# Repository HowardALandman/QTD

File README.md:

# QTD
Research project on Quantum Time Dilation, including theory and plans for an experiment to test it.
For theory, see the doc/QuantumTime.pdf (or .tex) file, and the references therein.
For photos, see FB album https://www.facebook.com/howard.a.landman/media_set?set=a.10153244377383214.1073741833.690298213&type=3 .

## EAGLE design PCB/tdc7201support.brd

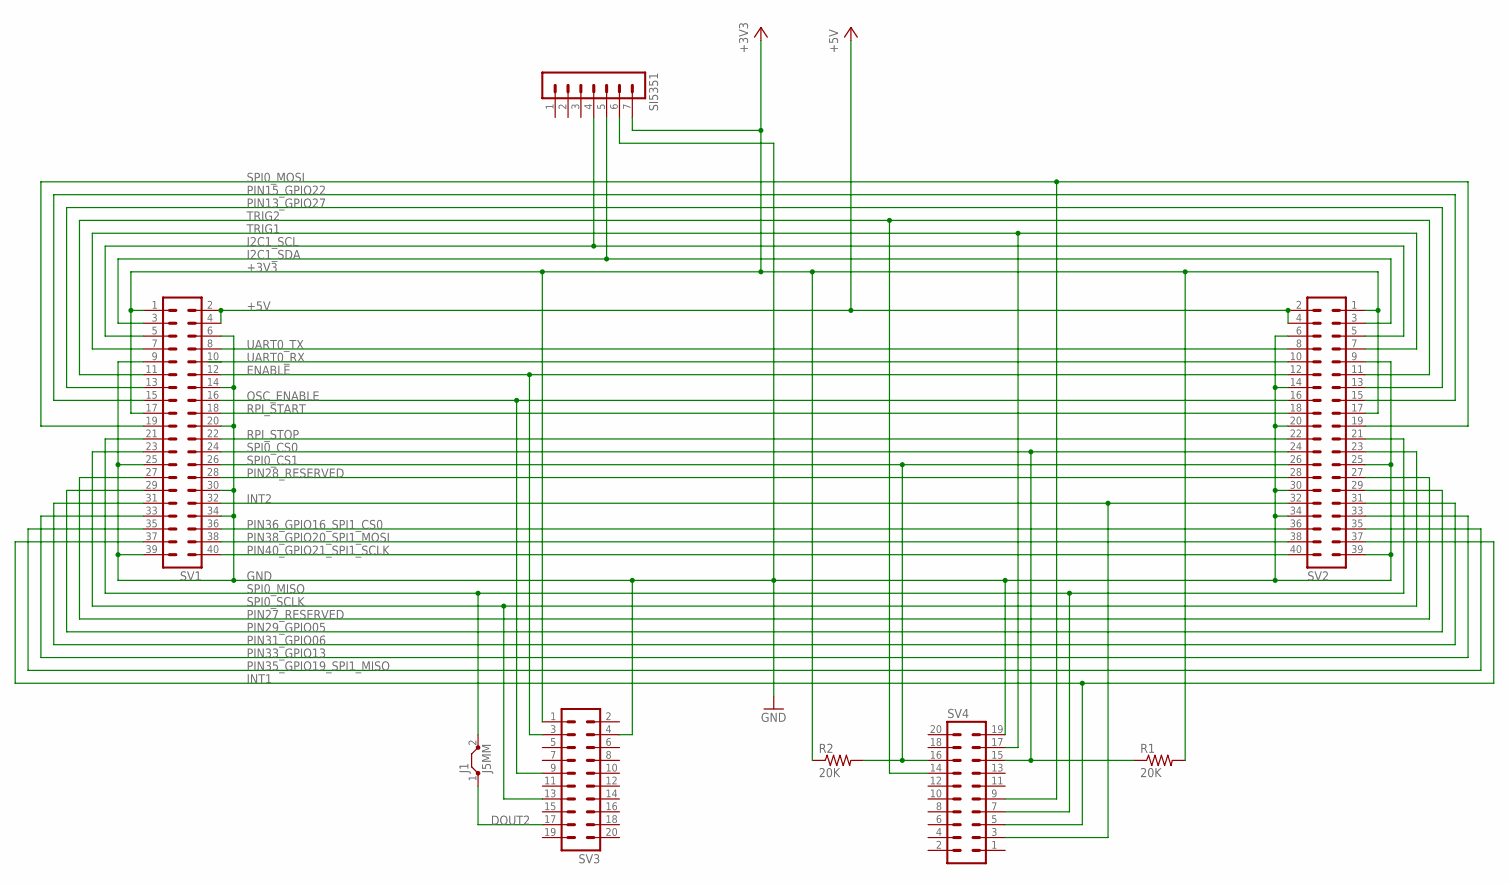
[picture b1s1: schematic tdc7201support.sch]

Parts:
J1: J5MM; 05
R1, R2: 20K; 0617/22
SI5351: MA07-1
SV1, SV2: MA20-2
SV3, SV4: MA10-2

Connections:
+3V3: R1.2, R2.1, SI5351.7, SV1.1, SV1.17, SV2.1, SV2.17, SV3.1
+5V: SV1.2, SV1.4, SV2.2, SV2.4
DOUT2: J1.1, SV3.17
ENABLE: SV1.12, SV2.12, SV3.3
GND: SI5351.6, SV1.6, SV1.9, SV1.14, SV1.20, SV1.25, SV1.30, SV1.34, SV1.39, SV2.6, SV2.9, SV2.14, SV2.20, SV2.25, SV2.30, SV2.34, SV2.39, SV3.4, SV4.19
I2C1_SCL: SI5351.4, SV1.5, SV2.5
I2C1_SDA: SI5351.5, SV1.3, SV2.3
INT1: SV1.37, SV2.37, SV4.5
INT2: SV1.32, SV2.32, SV4.3
OSC_ENABLE: SV1.16, SV2.16, SV3.9
PIN13_GPIO27: SV1.13, SV2.13
PIN15_GPIO22: SV1.15, SV2.15
PIN27_RESERVED: SV1.27, SV2.27
PIN28_RESERVED: SV1.28, SV2.28
PIN29_GPIO05: SV1.29, SV2.29
PIN31_GPIO06: SV1.31, SV2.31
PIN33_GPIO13: SV1.33, SV2.33
PIN35_GPIO19_SPI1_MISO: SV1.35, SV2.35
PIN36_GPIO16_SPI1_CS0: SV1.36, SV2.36
PIN38_GPIO20_SPI1_MOSI: SV1.38, SV2.38
PIN40_GPIO21_SPI1_SCLK: SV1.40, SV2.40
RPI_START: SV1.18, SV2.18
RPI_STOP: SV1.22, SV2.22
SPI0_CS0: R1.1, SV1.24, SV2.24, SV4.15
SPI0_CS1: R2.2, SV1.26, SV2.26, SV4.16
SPI0_MISO: J1.2, SV1.21, SV2.21, SV4.7
SPI0_MOSI: SV1.19, SV2.19, SV4.9
SPI0_SCLK: SV1.23, SV2.23, SV3.13
TRIG1: SV1.7, SV2.7, SV4.17
TRIG2: SV1.11, SV2.11, SV4.14
UART0_RX: SV1.10, SV2.10
UART0_TX: SV1.8, SV2.8

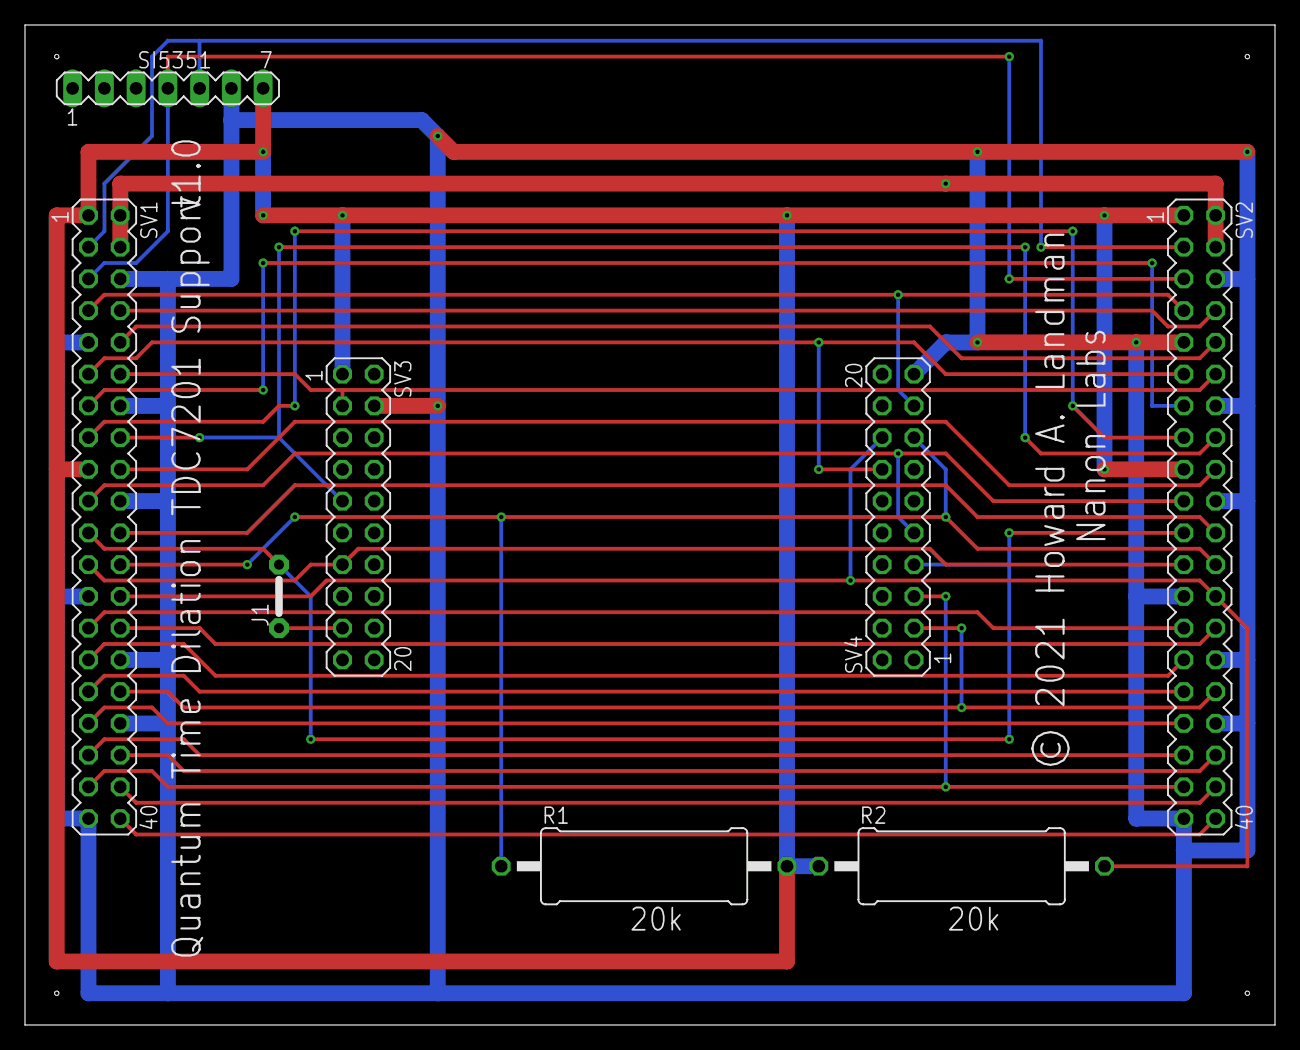
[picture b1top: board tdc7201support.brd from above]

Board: 2 copper layers, 100.0 x 80.0 mm, 8 parts (0 on the bottom side), 32 nets.

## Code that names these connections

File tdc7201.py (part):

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    # OSC_ENABLE turns on the EVM's clock generator chip.
    # It is a board function, not a chip function.
    # You don't need it if you are supplying an external clock.
    OSC_ENABLE = 16	# GPIO 23 = header pin 16 (arbitrary)
    #
    # The TRIGx signal indicates that the converter is ready to start.
    # Typically you would either use it to directly trigger some hardware,
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    # This can be because of success, or timeout; you need to read INT_STATUS
    # to determine which.
    # TRIG1 and INT1 only need to be set if you are using the #1 side of chip.
    TRIG1 = 7	# GPIO  4 = header pin  7  (arbitrary)
    INT1 = 37	# GPIO 26 = header pin 37 (arbitrary)
    # TRIG2 and INT2 only need to be set if you are using the #2 side of chip.
    TRIG2 = 11	# GPIO 17 = header pin 11 (arbitrary)
    INT2 = 32	# GPIO 12 = header pin 32 (arbitrary)

    # The START signal may be supplied externally to each side,
    # separately through START_EXT1 and START_EXT2 SMA connectors,
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    # The EVM brings it out separately.
    # Note that we CANNOT read side #2 of the chip in this configuration.
    # Don't need DOUT2 if only using side #1, but assign for completenes.
    #DOUT2 = 15	# GPIO  22 = header pin 15 (arbitrary)
 
    # TDC register address bit masks
    _AI = 0x80		# 0b10000000
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
	# Start the on-board clock generator running.
	# May not be necessary if you supply an external clock.
	GPIO.setup(self.OSC_ENABLE,GPIO.OUT,initial=GPIO.HIGH)
	print "Clock started (OSC_ENABLE = high) on pin", self.OSC_ENABLE, "."

	# Set up TRIG1 pin to know when chip is ready to measure.
	GPIO.setup(self.TRIG1,GPIO.IN)
	print "Set TRIG1 to input on pin", self.TRIG1, "."
	# Set up INT1 pin for interrupt-driven reads from tdc7201.
	GPIO.setup(self.INT1,GPIO.IN)
	print "Set INT1 to input on pin", self.INT1, "."

	# We're not using side #2 of the chip so far, but we wired these.
	# Set up TRIG2 pin to know when chip is ready to measure.
	GPIO.setup(self.TRIG2,GPIO.IN)
	print "Set TRIG2 to input on pin", self.TRIG2, "."
	# Set up INT2 pin for interrupt-driven reads from tdc7201.
	GPIO.setup(self.INT2,GPIO.IN)
	print "Set INT2 to input on pin", self.INT2, "."

	GPIO.setup(self.START,GPIO.OUT,initial=GPIO.LOW)
	print "Set START to output (low) on pin", self.START, "."
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    def measure(self):
	meas_start = time.time()
	# Check GPIO state doesn't indicate a measurement is happening.
	if (not GPIO.input(self.INT1)):
	    print "WARNING: INT1 already active (low)."
	if (GPIO.input(self.TRIG1)):
	    print "ERROR: TRIG1 already active (high)."
	    return
	# To start measurement, need to set START_MEAS in TDCx_CONFIG1 register.
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	self.write8(self.CONFIG1,cf1|self._CF1_START_MEAS)
	# Wait for TRIG1. This is inefficient, but OK for now.
	timeout = time.time() + 0.1	#Don't wait longer than a tenth of a second.
	while (not GPIO.input(self.TRIG1)) and (time.time() < timeout):
	    pass
	if GPIO.input(self.TRIG1):
	    print "Got trigger, issuing start."
	else:
	    print "Timed out waiting for trigger to rise."
	    return
	# Check that INT1 is inactive (high) as expected.
	if GPIO.input(self.INT1):
	    #print "INT1 is inactive (high) as expected."
	    pass
	else:
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	#time.sleep(0.000001)
	GPIO.output(self.START,GPIO.LOW)
	print "Generated START pulse."
	#if GPIO.input(self.INT1):
	#    #print "INT1 is inactive (high) as expected."
	#    pass
	#else:
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	#    return
	# Wait for TRIG1 to fall. This is inefficient, but OK for now.
	timeout = time.time() + 0.1	#Don't wait longer than a tenth of a second.
	while (GPIO.input(self.TRIG1)) and (time.time() < timeout):
	    pass
	if GPIO.input(self.TRIG1):
	    print "Timed out waiting for trigger to fall."
	    return
	else:
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	#time.sleep(0.000001)
	GPIO.output(self.STOP,GPIO.LOW)
	#print "Generated second STOP pulse."
	#if GPIO.input(self.INT1):
	#    print "INT1 is inactive (high) as expected."
	#else:
	#    print "ERROR: INT1 is active (low)!"
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	# Wait for INT1. This is inefficient, but OK for now.
	# INT1 is active low.
	timeout = time.time() + 0.1	#Don't wait longer than a tenth of a second.
	while ((GPIO.input(self.INT1)) and (time.time() < timeout)):
	    pass
	if GPIO.input(self.INT1):
	    print "Timed out waiting for INT1."
	    return
	else:
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
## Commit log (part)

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2015-07-27 Initial version 0.1, 2009/04/09
2015-07-27 Version 0.2, 2009/04/13
2015-07-27 Version 0.3, 2009/04/29
2015-07-27 Version 0.5, 2009/06/11
2015-07-27 Version 0.6, 2009/07/03
2015-07-27 Version 0.7, 2009/09/09
2015-07-27 Version 1.1, 2009/09/12
2015-07-27 Version 1.2, 2010/01/04
2015-07-27 Version 1.3, 2010/02/20
2015-07-27 Version 2.1, 2012/08/27
2015-07-27 First thoughts on the Teachspin muon lifetime device, 2012/09/10 This was emailed to John Harton and Stuart Field.
2015-07-31 Added reference to paper.
2015-07-31 3D printing data for plate support.
2015-09-15 Initial commit of detector frame pieces.
2015-09-15 Redesign of slot structure to make slots through and wider. (This is "Rev 3".)
2015-09-15 Initial commit of sphere support.
2015-09-17 Minor adjustments after first (partial, aborted) print. Make outer cylinder 0.2 mm smaller OD and 0.2 mm larger ID (it fit, but was pretty snug). Add fillet at flange join.
2015-10-12 Sphere support, redesigned in FreeCAD for milling from 155 mm Delrin rod.
2015-10-12 Sphere support, same as cyls3g version except 160 mm base. For 3D printing, also broke into 8 octants or edges, and laid them down sideways for better tensile strength. (Wedges 7 and 8 are identical 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
2017-10-16 Python driver for Texas Instruments tdc7201 time-to-digital converter chip. Uses spidev library for SPI communications. Initial commit successfully reads and writes 8-bit registers. No class definiti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
2017-10-16 Rearranged to put DOUT2 with SPI signals. Added some comments.
2017-10-16 Try reading some 24-bit registers. Set more signals for side #2.
2017-11-06 Added more class methods. Added code to do measurement and compute TOF1.
2017-11-06 Add files via upload
    version 3.0
2017-11-06 Added Foam Support
    Added a support structure to strengthen the foam board holding all the electronics. It uses a hyperboloid strut system, and is very strong. But it's quite large (over 400g of plastic), and warping ca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
2017-12-01 Stable working version before conversion to Python 3. Both START and STOP pulses generated by program. Measurement works, TOF calculation works, can emulate a decay pair.
2017-12-01 Converted from Python 2 to Python 3.
2017-12-01 Turned off some debugging print statements. Deleted spi_broken() since that bug was fixed. Added "_" in front of a few more class variables. This is now primary source; Python 2 version is secondary.
2017-12-03 Added foam support
    Added “QTD Foam Support”.
    Updated “QuantumTime.tex”.
2017-12-03 Reworked test code to produce 0 to 6 STOP pulses. Extended compute_TOFs() to handle up to 5 STOP pulses.
2018-05-16 Created src directory.
2020-03-31 Fixed "INTB1 still low" bug. Enhanced clear_status(). Call clear_status() after each measurement. Added status reporting to measure(). Collect status statistics. Added 22 uS timeout. Now getting abou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
2020-04-10 Add files via upload
    Version 0.2 of Magnitude paper
2020-04-11 v2.0 of Magnitude paper
2020-04-11 v3.0 of Magnitude paper
2020-04-11 v3.1 of Magnitude paper
2020-04-11 v4.0 of Magnitude paper
2020-04-11 v4.1 of Magnitude paper
2020-04-11 v4.3 of Magnitude paper
2020-04-17 Increased SPI clock speed to max. Improved error message for when no TDC7201 is connected.
2020-04-19 Removed tdc7201.py since all development is now Python 3.
2020-04-19 Made software simulation of top pulses optional. In real operation these will come from outside.
2020-04-21 Comment change only.
2020-04-23 Make tdc7201 code into an importable module. Break out non-library functionality into qtd.py. This version sort of works, but requires "import tdc7201.tdc7201 as tdc7201". Will try to fix that in nex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
2020-05-02 Minor changes for 0.1 beta and uploading to pypi.org for the first time.Z
2020-05-03 Deleted unused top level code. Added exception handling in case SPI is not enabled or can't be opened.
2020-05-04 Fix and test exception handling when SPI interface is not enabled.
2020-05-04 Added cpuinfo.
2020-05-04 Bump version to 0.1b3.
2020-05-04 Added calibration2_periods, avg_cycles, and num_stop arguments to on().
2020-05-04 Added clock_cnrt_stop argument to on().
2020-05-04 Added clock_cntr_stop, clock_cntr_ovf, and timeout arguments to on().
2020-05-05 Added README file.
2020-05-05 Made licenses consistent (both GPLv3+ now) and bumped version.
2020-05-05 Debugging README.md
2020-05-05 Moved settings, more `code` words, and some reorganization of README.md.
2020-05-05 Change setup.py to use README.md as long_description.
2020-05-05 Testing multi-line paragraphs.
2020-05-06 Added `falling` argument to on(), and updated README.
2020-05-06 Clarified defaults in README.
2020-05-06 Version 0.2b6
2020-05-06 Set long_description_content_type to text/markdown.
2020-05-06 Version 0.2b7
2020-05-06 Added arguments to initGPIO() so user can select pin assignments.
2020-05-06 Added arguments to initGPIO(), updated README.
2020-05-06 Minor fixes to README.
2020-05-06 Version 0.3b2
2020-05-10 Cleaned up indentation.
2020-05-10 Added measurement mode 1 and updated start.stop signals.
2020-05-10 Note that simulate does not work with averaging.
2020-05-10 Added averaging code to measurement mode 2 (does not work with simulate yet).
2020-05-11 Initial code for using MQTT to monitor CPU health etc.
2020-05-11 Fixed syntax error in measurement mode 1.
2020-05-12 Added payload decoding (from ASCII bytestream to Python string). Improved connect message.
2020-05-16 Added MQTT publish & subscribe functionality.
2020-05-16 SPI speedup using auto-increment mode.
2020-05-16 Version 0.5b2 : Fix home page URL
2020-05-21 Try harder to recover from INT1 errors.
2020-05-21 Publish driver, os_name. Fix batch so node-red pie chart works.
2020-05-22 Added PSI experiment plan v1.1.
2020-05-22 Fixed force mode in clear_status().
2020-05-22 Reorganized MQTT publishing into separate methods.
2020-05-23 Deleted extraneous period in README.md.
2020-05-25 Delinted, and added basic docstrings.
2020-05-28 Turn off some debug printing.
2020-05-29 Debugging temperature averaging.
2020-05-29 Massive de-linting. Use try-with-as for opening files and pipes.
2020-06-02 Pull version number from __init__.py to setup.py.
2020-06-03 Sped up publish_tdc7201_driver(), hopefully final version.
2020-06-03 Added SIGINT handling for more graceful exit. Doesn't clean up GPIO yet.
2020-06-05 Increased slot width 1 mm, decreased radius 1 mm, added filleting with 3 mm radius.
2020-06-05 Extended charts to 24 hours, added no-data labels.
2020-06-05 Added exact OS version date to publish_os_name().
2020-06-05 Improve mqtt behavior, add disconnect callback. Handle ^C interupt better.
2020-06-06 Fix missing 'self' argument in cleanup(). Improve TRIG1 error recovery.
2020-06-10 Keep cumulative statistics.
2020-06-10 Moved non-TDC status monitoring into a separate program pi_stats.py.
2020-06-10 Print a newline after keyboard interrupt before anything else.
2020-06-12 As printed at Prozix.
2020-06-13 Added publish_load_avg().
2020-06-16 Write data files, one per batch, with only successful measurements.
2020-06-18 Corrected typo "set_SPI_clock".
2020-06-18 Added read16() and write16() methods, used them, and updated documentation.
2020-06-19 Add register configs and raw results to data file.
2020-06-24 Put try:except: around opening data files. Reorder measurement data lines. Run SPI at 30 MHz.
2020-06-24 Allow absolute max SPI speed of 33 MHz, with warning if over 25 MHz.
2020-06-24 Version 0.7b4. Added exit() and used it.
2020-06-29 Check length of hw_pair. This is necessary to work on Raspbian Stretch.
2020-07-10 Fixed crash in MQTT when can't connect to server. Inserted space in TOF line.
2020-07-12 Cleaned up error printing in measure().
2020-07-12 Cleanup THEN and NOW. Allow prepending run # to error messages in measure().
2020-07-12 Enable writing error messages to data file.
2020-08-04 Require spidev>=3.5, as 3.4 had a Py_DECREF bug that could cause the program to die with "free(): invalid pointer" after 100M+ cycles.
2020-08-04 Moved constant padded xmit data out of read_regs8() and read_regs24(). This was to debug the "free(): invalid pointer" problem, but should be slightly faster, so I'm leaving it in.
2020-08-04 Restructure result_list & cum_results calculation. Write cum_results to end of data file. Set batch size to 100,000; can now read absolute numbers as percents.
2020-08-08 Add pulse pairs per second.
2020-08-08 Changed "qtd-0w" to generic "CPU". Changed mount point for USB drive to /mnt/qtd.
2020-08-08 Added read16().
2020-08-09 Reduce reset hold time from 0.1 S to 0.000001 S (1 uS). This should be safe as there is no minimum time in datasheet.
2020-08-09 Catch up to version 0.7b8.
2020-08-10 Bump version number (for documentation changes).
2020-08-10 Fixed formatting of off() and set_SPI_clock_speed(), which were messed up by preceding bulleted lists.
2020-08-10 Bump version (for documentation changes).
2020-08-10 Bumped version (for documentation changes).
2020-08-14 Version 0.8b2. Complete rewrite of TRIG handling. Added ability to set TRIGG_EDGE. Added code to handle TRIGG_EDGE being set. Deleted check for error 8 (unnecessary). Not seeing any error 11s either.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
2020-08-20 Try to fix formatting of on().
2020-09-07 pulse.py : added. qtd.py : Reworked TRIG handling to allow ignoring it when not simulating.
2020-09-07 Rework TRIG handling to allow ignoring it when not simulating. Added error numbers to all error messages in measure(). Fixed setting of overflow timeout when using retain_state.
2020-09-11 Only put out STOP pulses. Try to get about 2 pulses per set.
2020-09-14 Initial release. Reads files fine, but no processing of data yet.
2020-09-14 Guarantee at least 2 pulses per window.
2020-09-17 Eliminate register reads and minimize register writes inside measure(). Skip 8-bit masking in write8(). Delete error 13 and error 11 checks (they were never really necessary).
2020-09-22 v4.5 of Magnitude paper
2020-10-02 Fixed off-by-1 list slicing in error message.
2020-10-04 Reduce on() wait time to 1.5 mS.
2020-10-09 Return SPI clock speed to 25 MHz, since faster does not improve performance much.
2020-10-09 Update sample usage to use on() and configure() correctly.
2020-10-09 Fix "Settings" paragraph to match refactoring of on() and configure().
2020-10-10 Don't print (just log) on error 6.
2020-10-14 First commit of configure_new_machine.sh. Run this in a fresh raspbian to set up machine for QTD.
2020-10-17 Version 0.9.0 (switch to SemVer version numbers). Use GPIO.wait_for_edge() for INT1; slightly slower but much lower power.
2020-10-18 Cut measurement timeout to 165 uS.
2020-10-18 Changed temperature limits in CPU Temp Gauge to reflect thermal problems seen.
2020-10-19 Rewrite measure() timeout discussion to match v.0.10.0.
2020-11-17 v0.10.1 Fixed formatting error in configure() in README.
2020-11-20 Programs and writeup from 2012 Teachspin experiment.
2020-11-23 Handle OSError thrown by trying to open a new file when disk full.
2020-11-23 Fix except condition when failing to open log file for writing.
2020-11-26 v0.11.0 Add count_pulses() and use it. This speeds up measure() by about 15%.
2020-11-26 Adjustments for tdc7201 library v0.11.0.
2020-11-26 v0.11.1
2020-11-26 v0.11.2 More fixes to README.md.
2020-12-04 Add system hardware diagram.
2020-12-28 v5.1 as submitted to General Relativity and Gravitation
2020-12-28 Minor changes to clarify MeV (energy) versus MeV/c (momentum).
2021-03-08 Change MQTT server to test.mosquitto.org.
2021-07-31 First Si5351 support. Add Si5351.py. Modify configure_new_machine.sh to include setup for 5351 support.
2021-07-31 Clean up, comments, and delete unused lines.
2021-08-12 Add support for Adafruit Si5351 and ADS1115.
2021-08-13 Added voltage tab and 3 voltage rail graphs. Changed some warning thresholds and colors.
2021-11-04 Show how to make node-red pretty print, and to uninstall tdc7201 lib if needed.
2021-11-04 Add support for I2C bus devices (Si5351 and ads1115). Report voltages if ads1115 present.

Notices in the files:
PCB/tdc7201support.brd:
© 2021 Howard A. Landman
